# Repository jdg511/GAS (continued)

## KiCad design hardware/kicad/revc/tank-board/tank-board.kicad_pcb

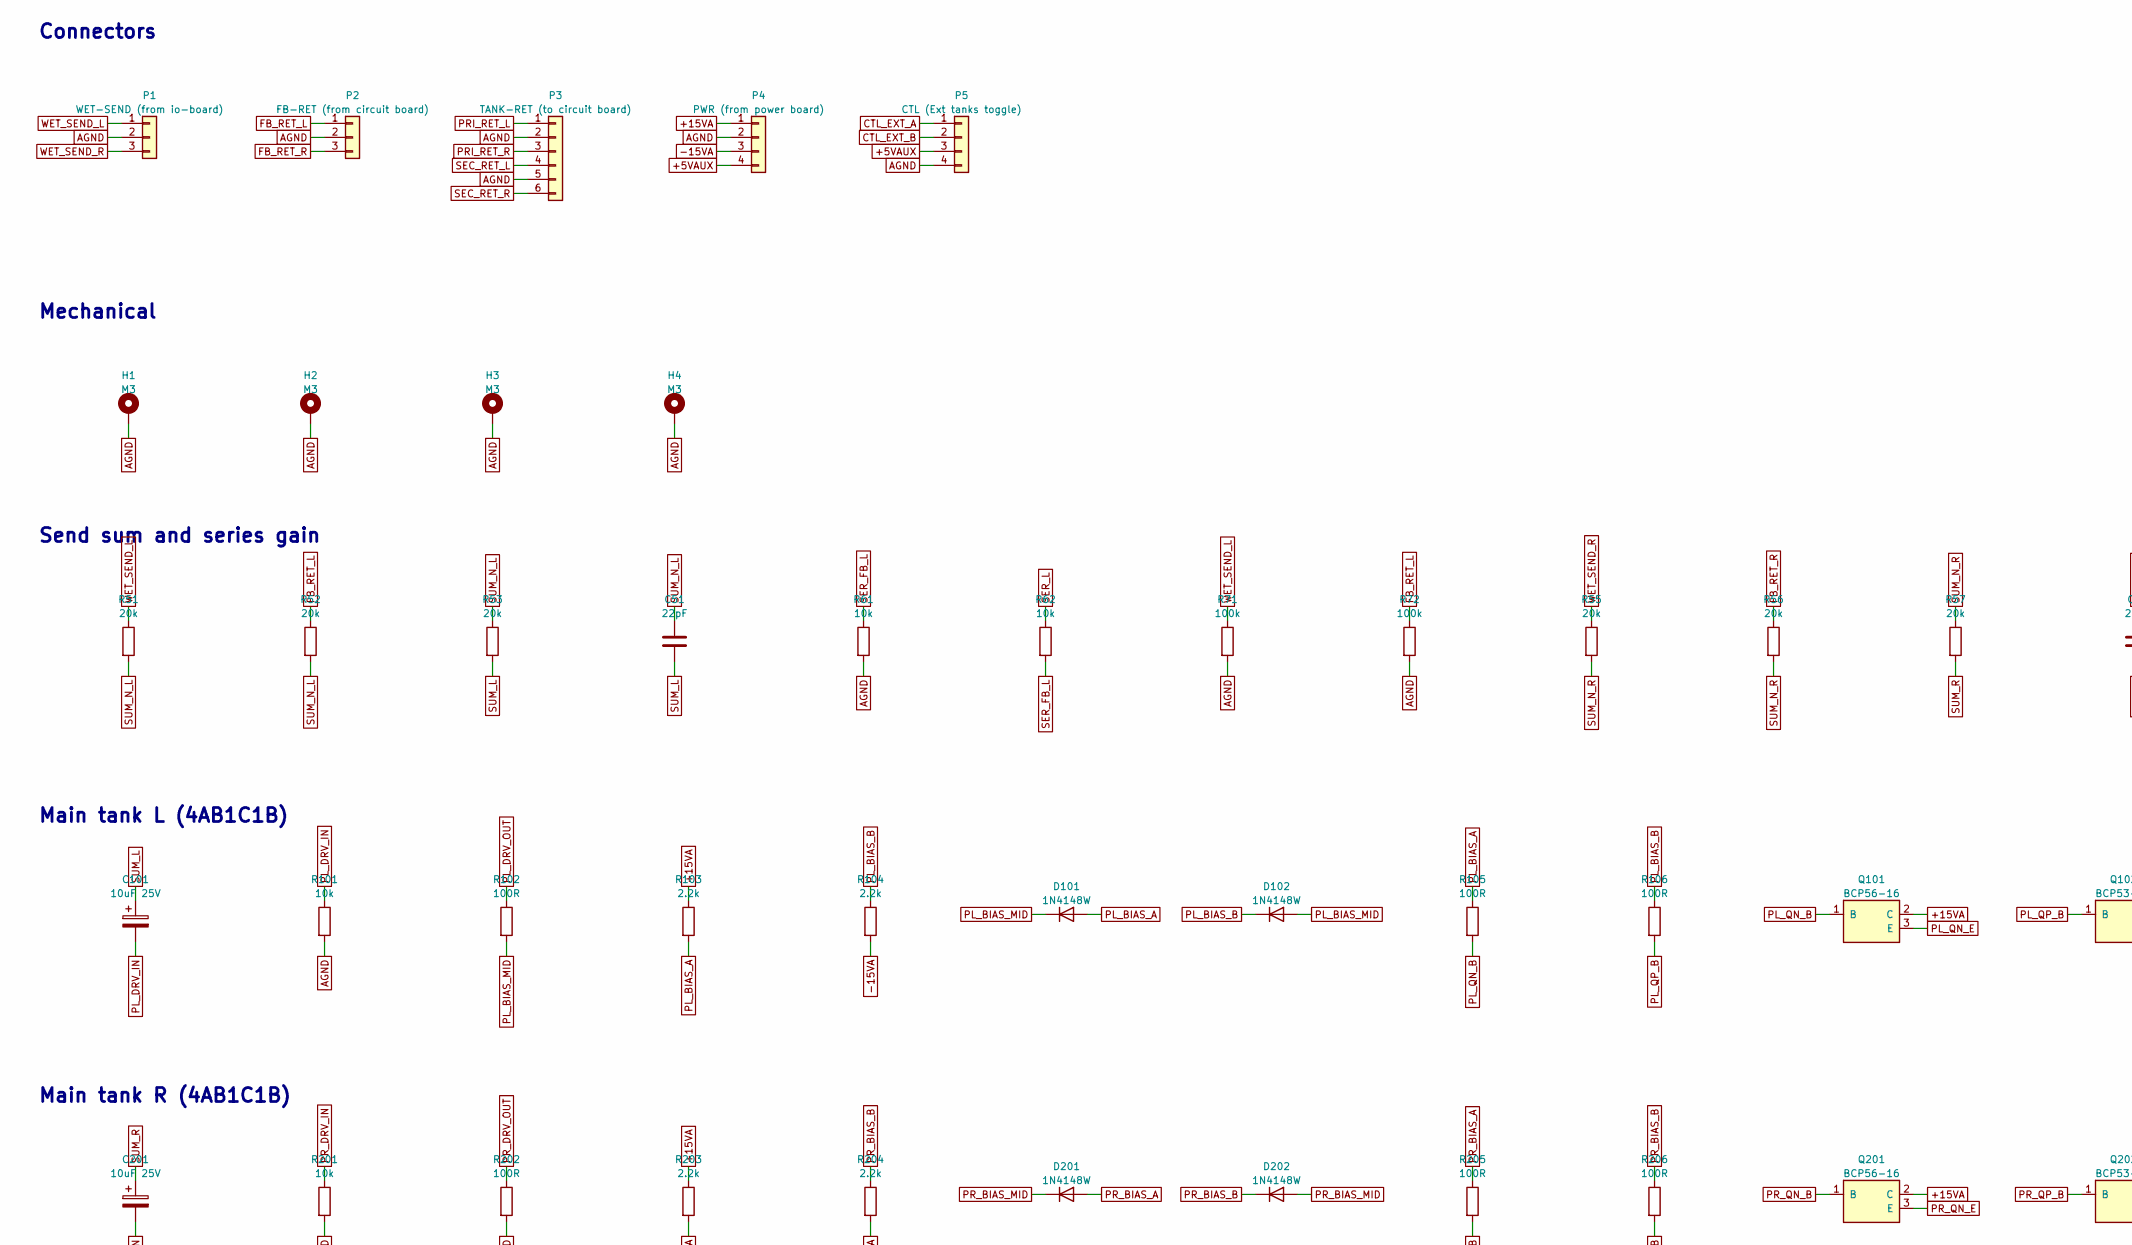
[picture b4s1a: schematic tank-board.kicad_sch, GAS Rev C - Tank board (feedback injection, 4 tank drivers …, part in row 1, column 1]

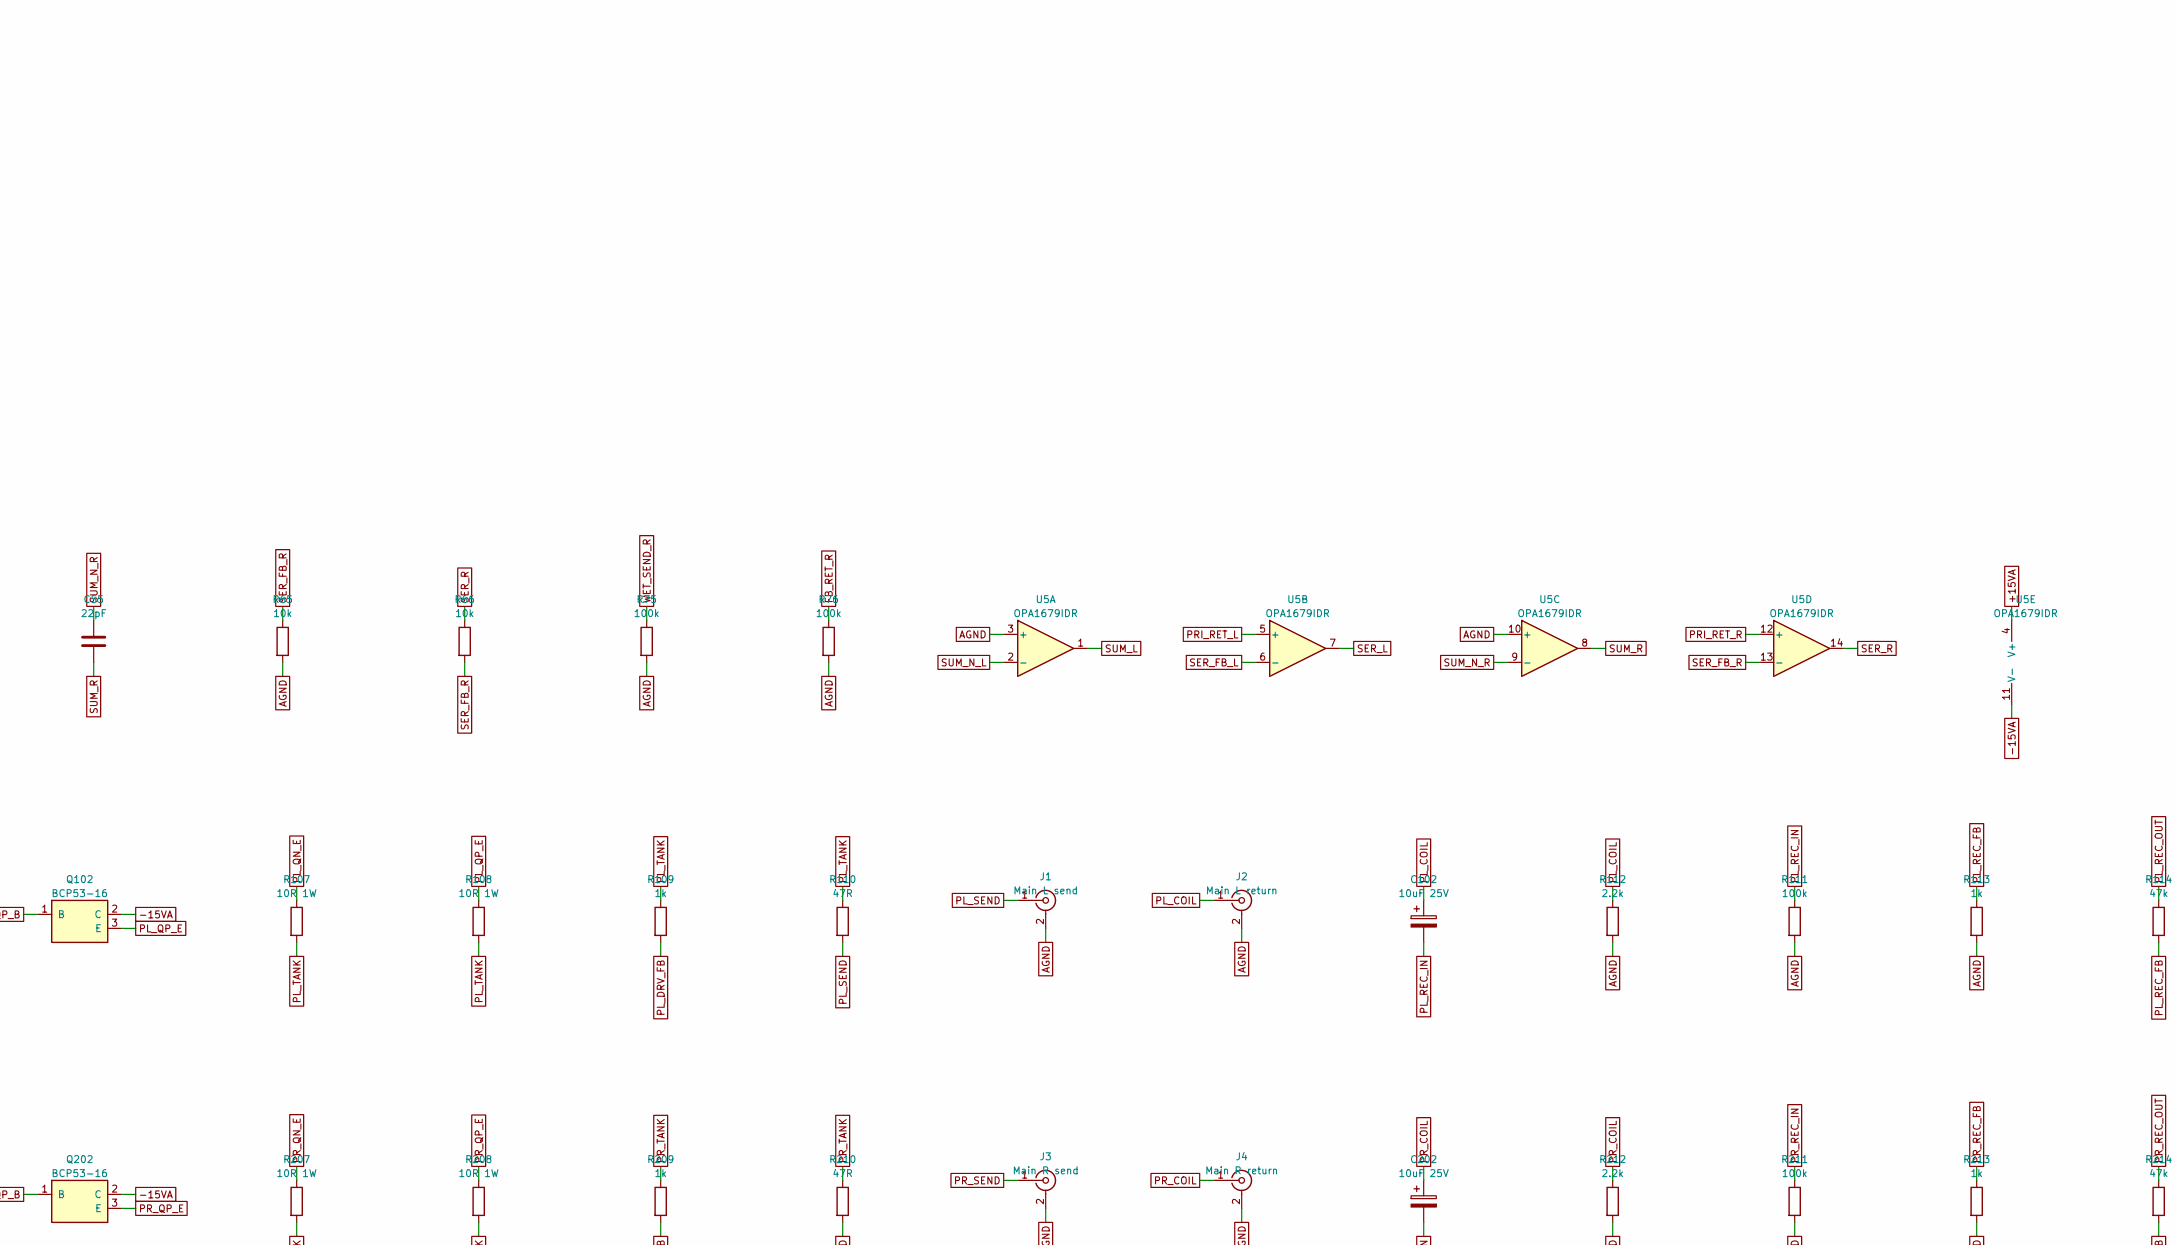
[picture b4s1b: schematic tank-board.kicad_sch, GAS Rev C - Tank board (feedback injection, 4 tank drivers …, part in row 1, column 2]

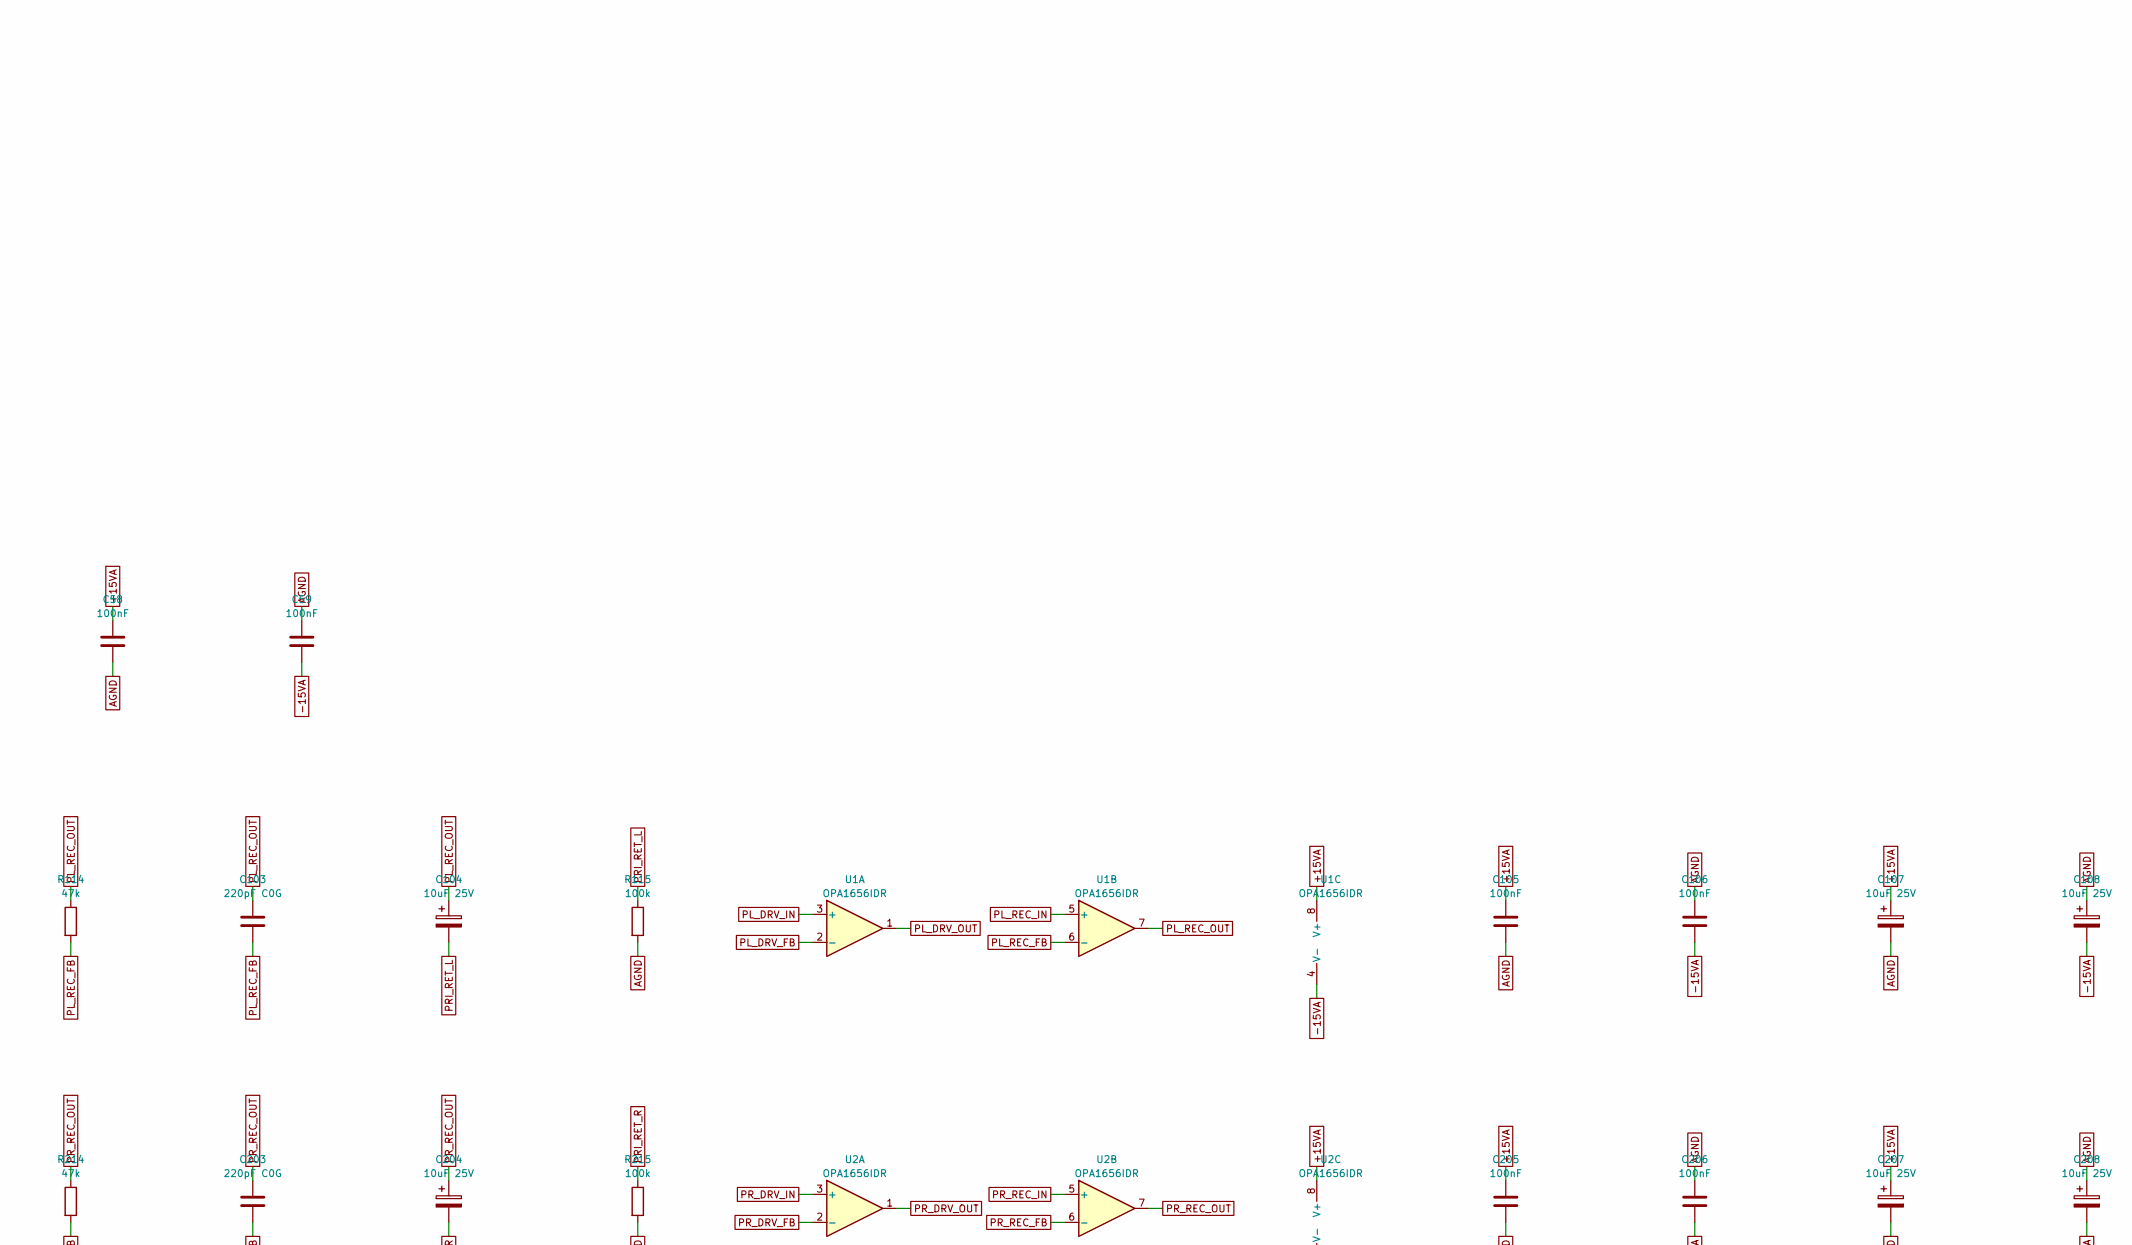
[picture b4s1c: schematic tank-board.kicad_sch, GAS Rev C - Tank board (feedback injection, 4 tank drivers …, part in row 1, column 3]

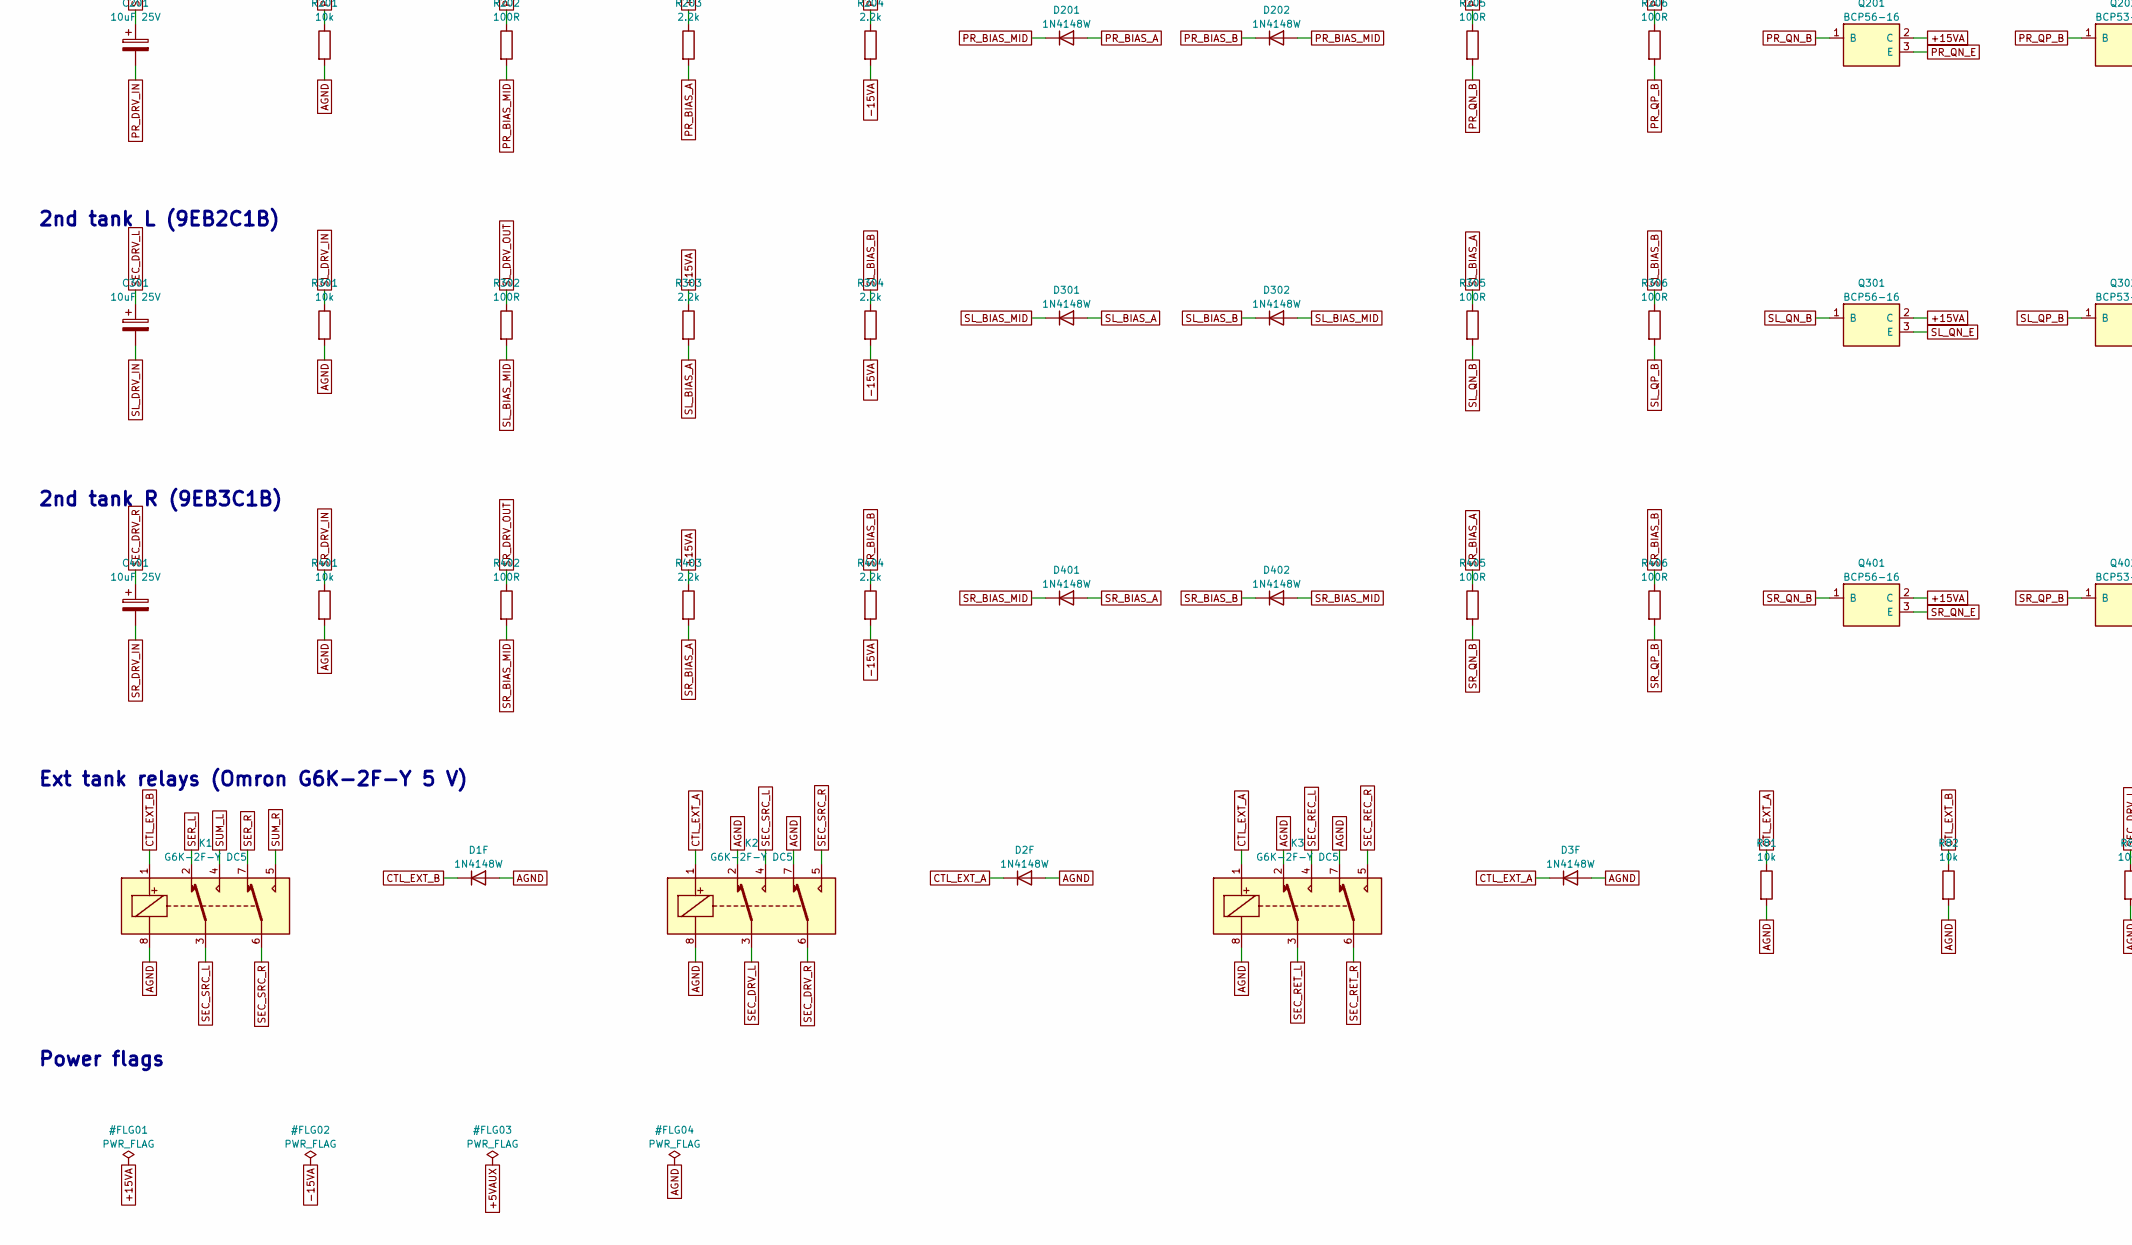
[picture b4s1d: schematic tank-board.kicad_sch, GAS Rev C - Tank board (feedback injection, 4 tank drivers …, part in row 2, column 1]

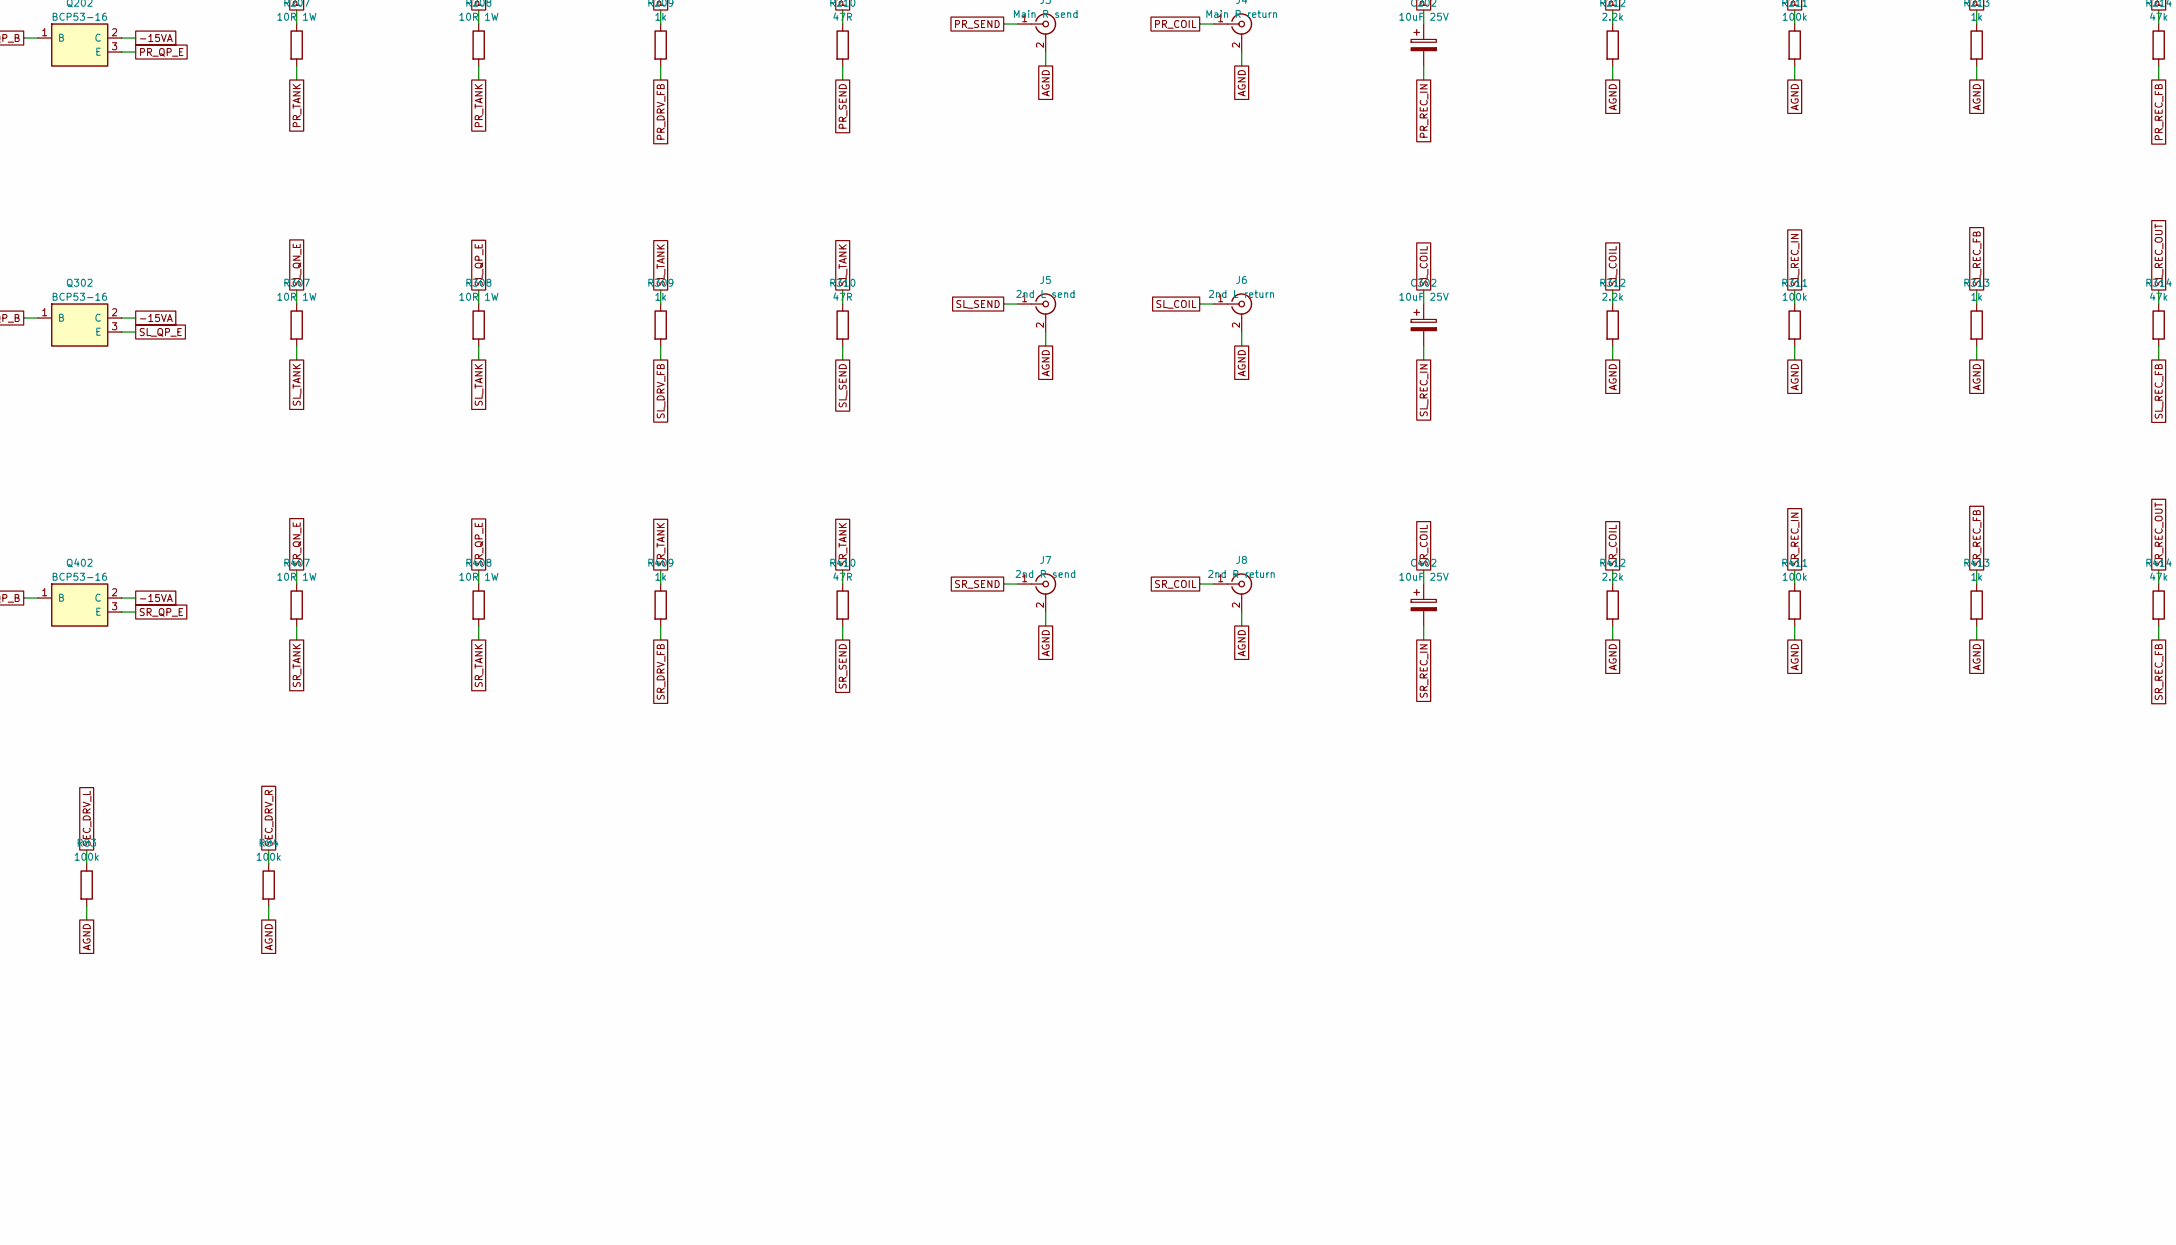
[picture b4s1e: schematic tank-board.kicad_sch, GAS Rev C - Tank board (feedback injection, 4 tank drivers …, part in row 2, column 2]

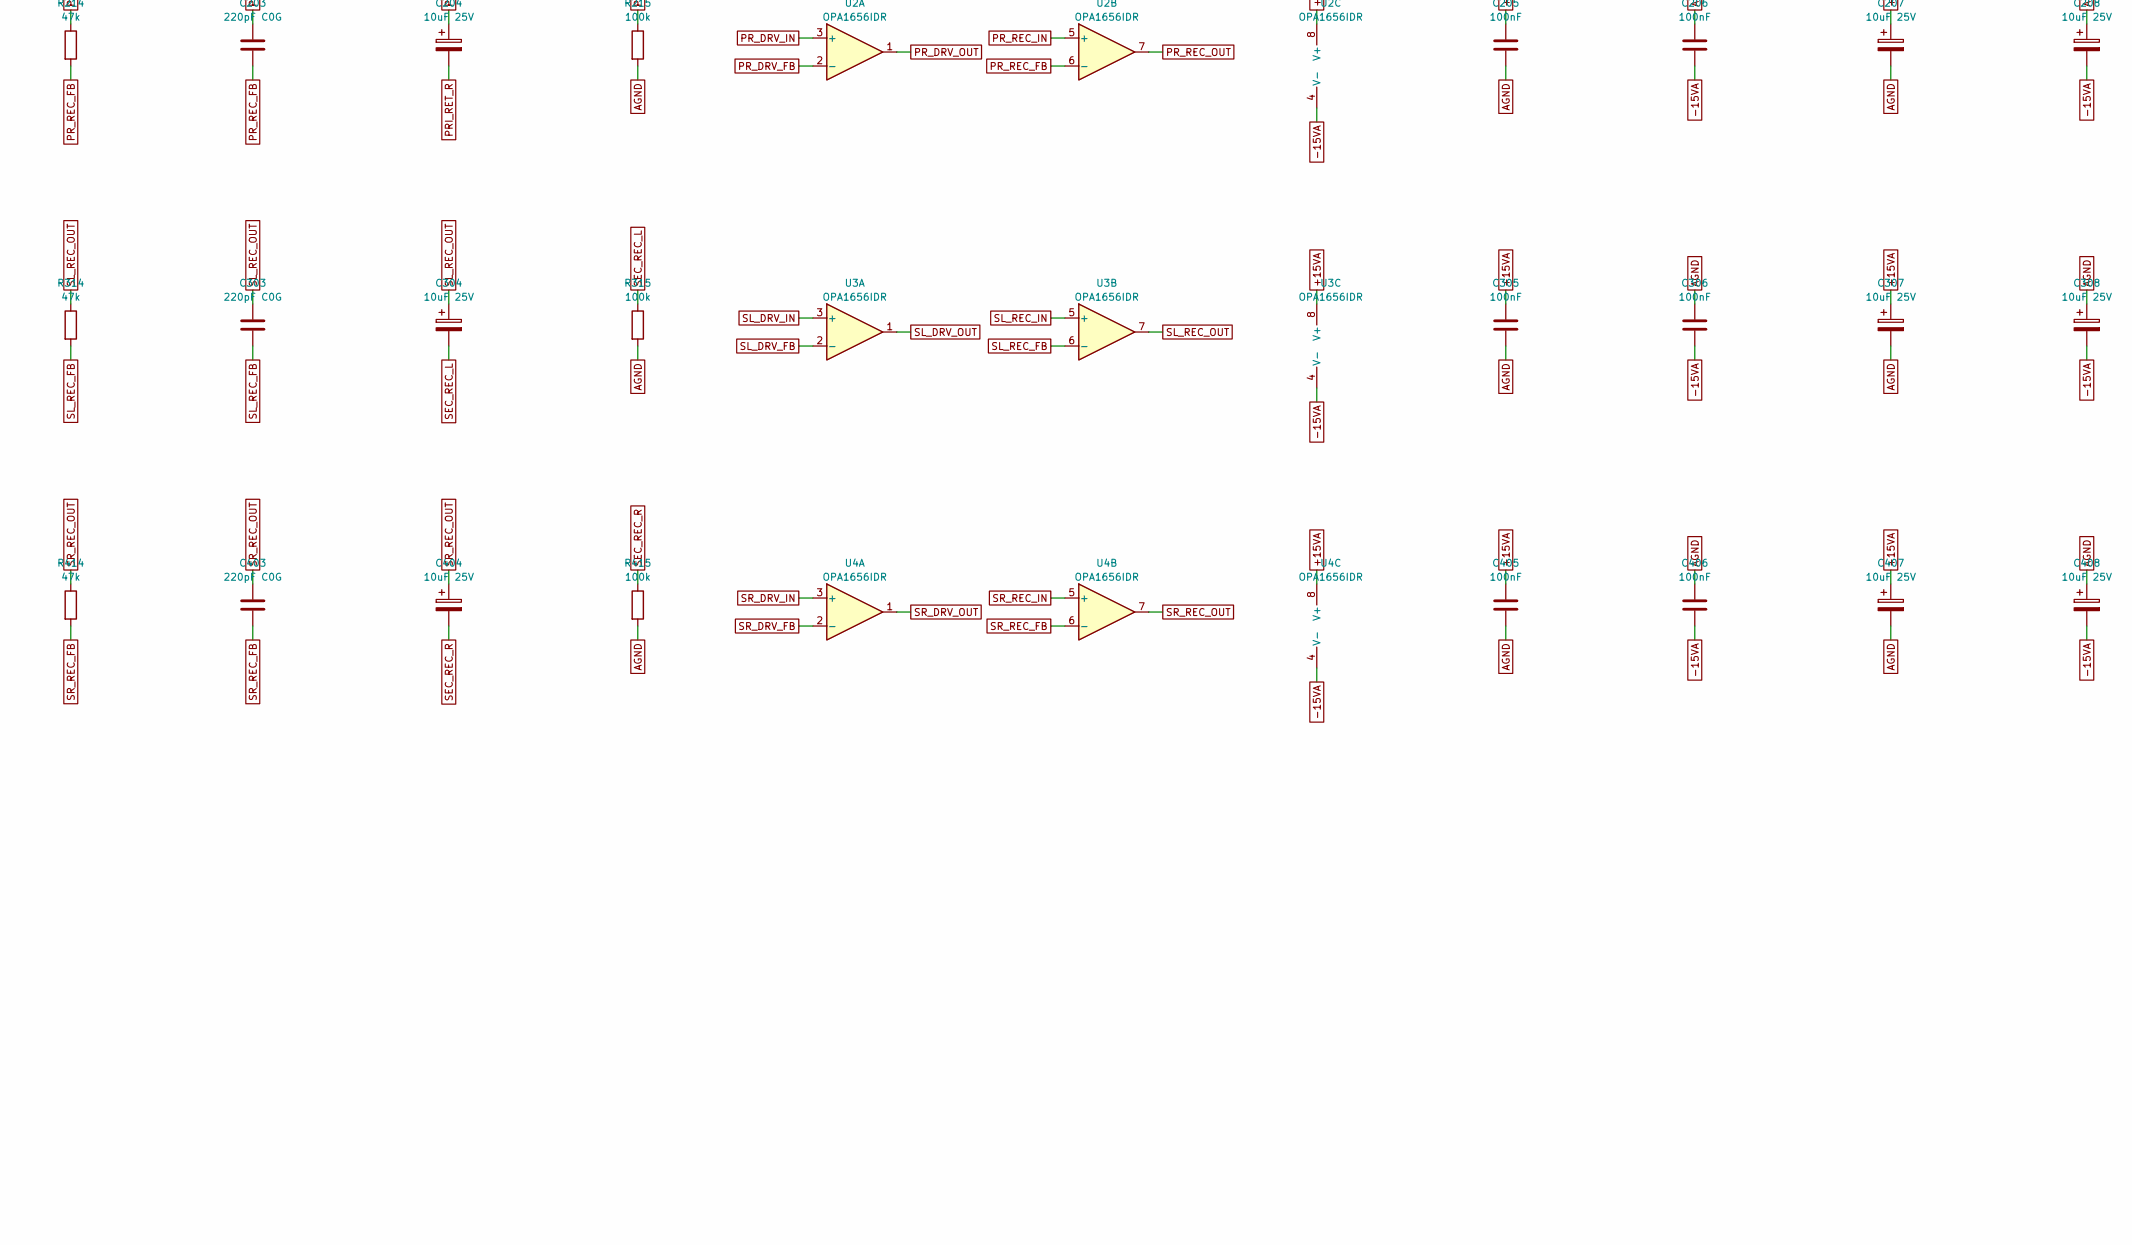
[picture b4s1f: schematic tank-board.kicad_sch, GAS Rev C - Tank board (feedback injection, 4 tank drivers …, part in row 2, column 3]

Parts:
C51, C55: 22pF; C_0603_1608Metric; MPN CL10C220JB8NNNC
C58, C59, C105, C106, C205, C206, C305, C306, C405, C406: 100nF; C_0603_1608Metric; MPN CL10B104KB8NNNC
C101, C102, C104, C107, C108, C201, C202, C204, C207, C208, C301, C302, C304, C307, C308, C401, C402, C404, C407, C408: 10uF 25V; CP_Elec_5x5.8; MPN UWT1E100MCL1GB
C103, C203, C303, C403: 220pF C0G; C_0603_1608Metric; MPN CL10C221JB8NNNC
D1F, D2F, D3F, D101, D102, D201, D202, D301, D302, D401, D402: 1N4148W; D_SOD-123; MPN 1N4148W-7-F
H1, H2, H3, H4: M3; MountingHole_3.2mm_M3_Pad_Via
J1: Main L send; Jack_RCA_SameSky_RCJ-041_Horizontal; MPN RCJ-041
J2: Main L return; Jack_RCA_SameSky_RCJ-041_Horizontal; MPN RCJ-041
J3: Main R send; Jack_RCA_SameSky_RCJ-041_Horizontal; MPN RCJ-041
J4: Main R return; Jack_RCA_SameSky_RCJ-041_Horizontal; MPN RCJ-041
J5: 2nd L send; Jack_RCA_SameSky_RCJ-041_Horizontal; MPN RCJ-041
J6: 2nd L return; Jack_RCA_SameSky_RCJ-041_Horizontal; MPN RCJ-041
J7: 2nd R send; Jack_RCA_SameSky_RCJ-041_Horizontal; MPN RCJ-041
J8: 2nd R return; Jack_RCA_SameSky_RCJ-041_Horizontal; MPN RCJ-041
K1, K2, K3: G6K-2F-Y DC5; Relay_DPDT_Omron_G6K-2F-Y; MPN G6K-2F-Y DC5
P1: WET-SEND (from io-board); JST_XH_B3B-XH-A_1x03_P2.50mm_Vertical; MPN B3B-XH-A(LF)(SN)
P2: FB-RET (from circuit board); JST_XH_B3B-XH-A_1x03_P2.50mm_Vertical; MPN B3B-XH-A(LF)(SN)
P3: TANK-RET (to circuit board); JST_XH_B6B-XH-A_1x06_P2.50mm_Vertical; MPN B6B-XH-A(LF)(SN)
P4: PWR (from power board); JST_VH_B4P-VH_1x04_P3.96mm_Vertical; MPN B4P-VH(LF)(SN)
P5: CTL (Ext tanks toggle); JST_XH_B4B-XH-A_1x04_P2.50mm_Vertical; MPN B4B-XH-A(LF)(SN)
Q101, Q201, Q301, Q401: BCP56-16; SOT-223-3_TabPin2; MPN BCP56-16T1G
Q102, Q202, Q302, Q402: BCP53-16; SOT-223-3_TabPin2; MPN BCP53-16T1G
R51, R52, R53, R55, R56, R57: 20k; R_0603_1608Metric; MPN RC0603FR-0720KL
R61, R62, R65, R66, R81, R82, R101, R201, R301, R401: 10k; R_0603_1608Metric; MPN RC0603FR-0710KL
R71, R72, R75, R76, R83, R84, R111, R115, R211, R215, R311, R315, R411, R415: 100k; R_0603_1608Metric; MPN RC0603FR-07100KL
R102, R105, R106, R202, R205, R206, R302, R305, R306, R402, R405, R406: 100R; R_0603_1608Metric; MPN RC0603FR-07100RL
R103, R104, R112, R203, R204, R212, R303, R304, R312, R403, R404, R412: 2.2k; R_0603_1608Metric; MPN RC0603FR-072K2L
R107, R108, R207, R208, R307, R308, R407, R408: 10R 1W; R_2512_6332Metric; MPN RC2512FK-0710RL
R109, R113, R209, R213, R309, R313, R409, R413: 1k; R_0603_1608Metric; MPN RC0603FR-071KL
R110, R210, R310, R410: 47R; R_1206_3216Metric; MPN RC1206FR-0747RL
R114, R214, R314, R414: 47k; R_0603_1608Metric; MPN RC0603FR-0747KL
U1, U2, U3, U4: OPA1656IDR; SOIC-8_3.9x4.9mm_P1.27mm; MPN OPA1656IDR
U5: OPA1679IDR; SOIC-14_3.9x8.7mm_P1.27mm; MPN OPA1679IDR

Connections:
+5VAUX: P4.4, P5.3
+15VA: C58.1, C105.1, C107.1, C205.1, C207.1, C305.1, C307.1, C405.1, C407.1, P4.1, Q101.2 (C), Q201.2 (C), Q301.2 (C), Q401.2 (C), R103.1, R203.1, R303.1, R403.1, U1.8 (V+), U2.8 (V+), U3.8 (V+), U4.8 (V+), U5.4 (V+)
-15VA: C59.2, C106.2, C108.2, C206.2, C208.2, C306.2, C308.2, C406.2, C408.2, P4.3, Q102.2 (C), Q202.2 (C), Q302.2 (C), Q402.2 (C), R104.2, R204.2, R304.2, R404.2, U1.4 (V-), U2.4 (V-), U3.4 (V-), U4.4 (V-), U5.11 (V-)
AGND: C58.2, C59.1, C105.2, C106.1, C107.2, C108.1, C205.2, C206.1, C207.2, C208.1, C305.2, C306.1, C307.2, C308.1, C405.2, C406.1, C407.2, C408.1, D1F.2 (A), D2F.2 (A), D3F.2 (A), H1.1, H2.1, H3.1, H4.1, J1.2 (Ext), J2.2 (Ext), J3.2 (Ext), J4.2 (Ext), J5.2 (Ext), J6.2 (Ext), J7.2 (Ext), J8.2 (Ext), K1.8, K2.2, K2.7, K2.8, K3.2, K3.7, K3.8, P1.2, P2.2, P3.2, P3.5, P4.2, P5.4, R61.2, R65.2, R71.2, R72.2, R75.2, R76.2, R81.2, R82.2, R83.2, R84.2, R101.2, R111.2, R112.2, R113.2, R115.2, R201.2, R211.2, R212.2, R213.2, R215.2, R301.2, R311.2, R312.2, R313.2, R315.2, R401.2, R411.2, R412.2, R413.2, R415.2, U5.3 (+), U5.10 (+)
CTL_EXT_A: D2F.1 (K), D3F.1 (K), K2.1, K3.1, P5.1, R81.1
CTL_EXT_B: D1F.1 (K), K1.1, P5.2, R82.1
FB_RET_L: P2.1, R52.1, R72.1
FB_RET_R: P2.3, R56.1, R76.1
PL_BIAS_A: D101.2 (A), R103.2, R105.1
PL_BIAS_B: D102.1 (K), R104.1, R106.1
PL_BIAS_MID: D101.1 (K), D102.2 (A), R102.2
PL_COIL: C102.1, J2.1 (In), R112.1
PL_DRV_FB: R109.2, U1.2 (-)
PL_DRV_IN: C101.2, R101.1, U1.3 (+)
PL_DRV_OUT: R102.1, U1.1
PL_QN_B: Q101.1 (B), R105.2
PL_QN_E: Q101.3 (E), R107.1
PL_QP_B: Q102.1 (B), R106.2
PL_QP_E: Q102.3 (E), R108.1
PL_REC_FB: C103.2, R113.1, R114.2, U1.6 (-)
PL_REC_IN: C102.2, R111.1, U1.5 (+)
PL_REC_OUT: C103.1, C104.1, R114.1, U1.7
PL_SEND: J1.1 (In), R110.2
PL_TANK: R107.2, R108.2, R109.1, R110.1
PRI_RET_L: C104.2, P3.1, R115.1, U5.5 (+)
PRI_RET_R: C204.2, P3.3, R215.1, U5.12 (+)
PR_BIAS_A: D201.2 (A), R203.2, R205.1
PR_BIAS_B: D202.1 (K), R204.1, R206.1
PR_BIAS_MID: D201.1 (K), D202.2 (A), R202.2
PR_COIL: C202.1, J4.1 (In), R212.1
PR_DRV_FB: R209.2, U2.2 (-)
PR_DRV_IN: C201.2, R201.1, U2.3 (+)
PR_DRV_OUT: R202.1, U2.1
PR_QN_B: Q201.1 (B), R205.2
PR_QN_E: Q201.3 (E), R207.1
PR_QP_B: Q202.1 (B), R206.2
PR_QP_E: Q202.3 (E), R208.1
PR_REC_FB: C203.2, R213.1, R214.2, U2.6 (-)
PR_REC_IN: C202.2, R211.1, U2.5 (+)
PR_REC_OUT: C203.1, C204.1, R214.1, U2.7
PR_SEND: J3.1 (In), R210.2
PR_TANK: R207.2, R208.2, R209.1, R210.1
SEC_DRV_L: C301.1, K2.3, R83.1
SEC_DRV_R: C401.1, K2.6, R84.1
SEC_REC_L: C304.2, K3.4, R315.1
SEC_REC_R: C404.2, K3.5, R415.1
SEC_RET_L: K3.3, P3.4
SEC_RET_R: K3.6, P3.6
SEC_SRC_L: K1.3, K2.4
SEC_SRC_R: K1.6, K2.5
SER_FB_L: R61.1, R62.2, U5.6 (-)
SER_FB_R: R65.1, R66.2, U5.13 (-)
SER_L: K1.2, R62.1, U5.7
SER_R: K1.7, R66.1, U5.14
SL_BIAS_A: D301.2 (A), R303.2, R305.1
SL_BIAS_B: D302.1 (K), R304.1, R306.1
SL_BIAS_MID: D301.1 (K), D302.2 (A), R302.2
SL_COIL: C302.1, J6.1 (In), R312.1
SL_DRV_FB: R309.2, U3.2 (-)
SL_DRV_IN: C301.2, R301.1, U3.3 (+)
SL_DRV_OUT: R302.1, U3.1
SL_QN_B: Q301.1 (B), R305.2
SL_QN_E: Q301.3 (E), R307.1
SL_QP_B: Q302.1 (B), R306.2
SL_QP_E: Q302.3 (E), R308.1
SL_REC_FB: C303.2, R313.1, R314.2, U3.6 (-)
SL_REC_IN: C302.2, R311.1, U3.5 (+)
SL_REC_OUT: C303.1, C304.1, R314.1, U3.7
SL_SEND: J5.1 (In), R310.2
SL_TANK: R307.2, R308.2, R309.1, R310.1
SR_BIAS_A: D401.2 (A), R403.2, R405.1
SR_BIAS_B: D402.1 (K), R404.1, R406.1
SR_BIAS_MID: D401.1 (K), D402.2 (A), R402.2
SR_COIL: C402.1, J8.1 (In), R412.1
SR_DRV_FB: R409.2, U4.2 (-)
SR_DRV_IN: C401.2, R401.1, U4.3 (+)
SR_DRV_OUT: R402.1, U4.1
SR_QN_B: Q401.1 (B), R405.2
SR_QN_E: Q401.3 (E), R407.1
SR_QP_B: Q402.1 (B), R406.2
SR_QP_E: Q402.3 (E), R408.1
SR_REC_FB: C403.2, R413.1, R414.2, U4.6 (-)
SR_REC_IN: C402.2, R411.1, U4.5 (+)
SR_REC_OUT: C403.1, C404.1, R414.1, U4.7
SR_SEND: J7.1 (In), R410.2
SR_TANK: R407.2, R408.2, R409.1, R410.1
SUM_L: C51.2, C101.1, K1.4, R53.2, U5.1
SUM_N_L: C51.1, R51.2, R52.2, R53.1, U5.2 (-)
SUM_N_R: C55.1, R55.2, R56.2, R57.1, U5.9 (-)
SUM_R: C55.2, C201.1, K1.5, R57.2, U5.8
WET_SEND_L: P1.1, R51.1, R71.1
WET_SEND_R: P1.3, R55.1, R75.1

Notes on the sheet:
Connectors
Mechanical
Send sum and series gain
Main tank L (4AB1C1B)
Main tank R (4AB1C1B)
2nd tank L (9EB2C1B)
2nd tank R (9EB3C1B)
Ext tank relays (Omron G6K-2F-Y 5 V)
Power flags

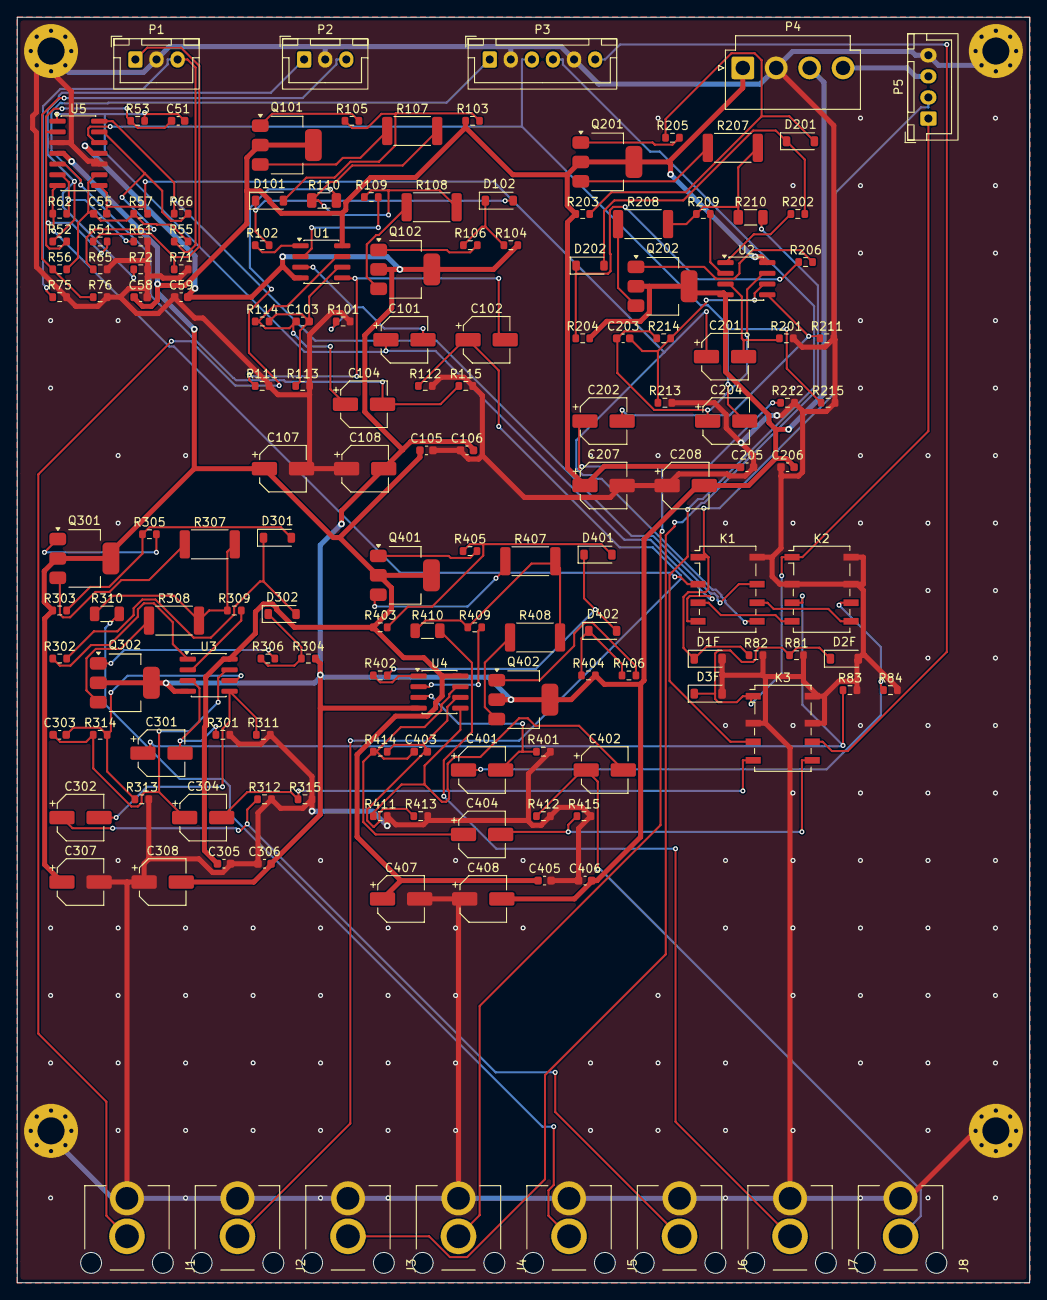
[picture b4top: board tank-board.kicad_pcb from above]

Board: 2 copper layers, 120.0 x 150.0 mm, 158 parts (0 on the bottom side), 92 nets.
